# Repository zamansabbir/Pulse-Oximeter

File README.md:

# Pulse-Oximeter
This repository contains Firmware (driver) for PPG device made using PSOC1 chip to operate MAX30102 for collecting PPG signal and calculating SPO2. The device is dynamically tuned to address the technical reliability  issues involving PPG signal on people with dark skin tones.  

PPG_Firmware_6->Main.c files contains driver API for MAX30102

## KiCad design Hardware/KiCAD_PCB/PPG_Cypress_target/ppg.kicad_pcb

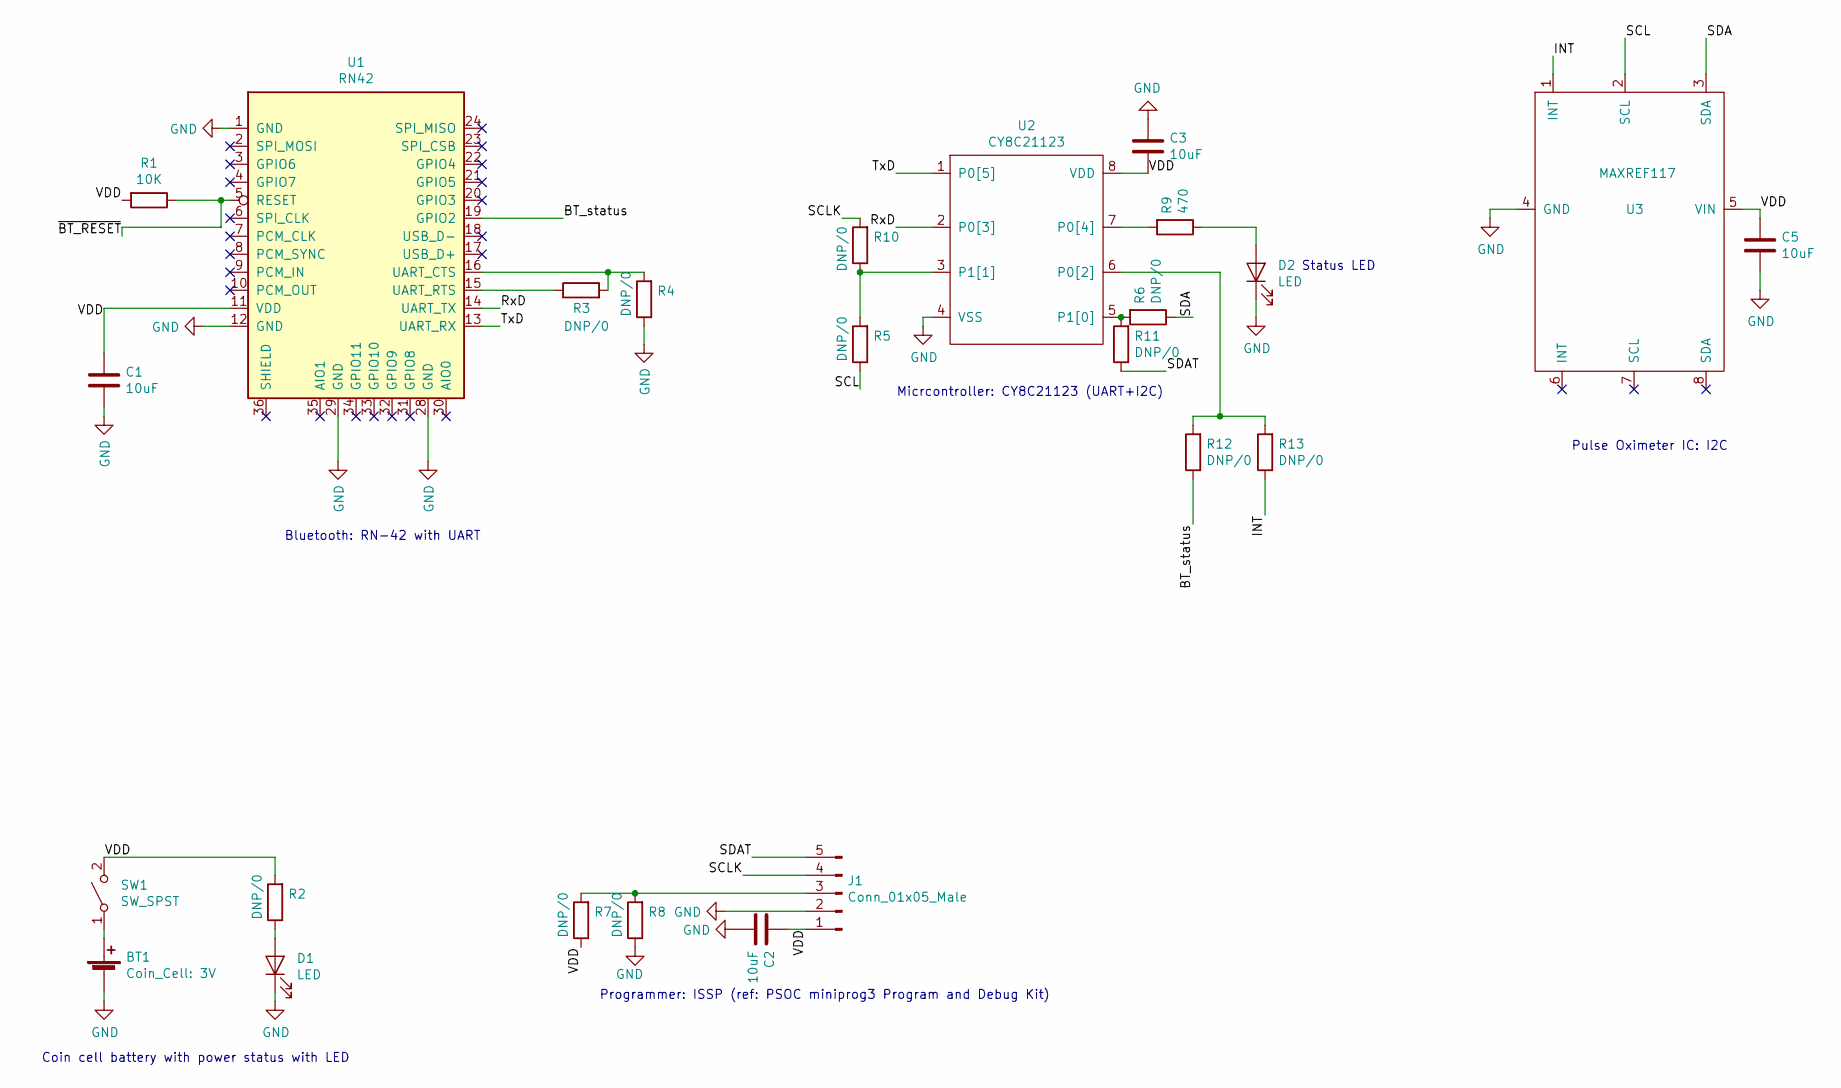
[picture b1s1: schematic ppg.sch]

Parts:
BT1: Coin_Cell: 3V; BatteryHolder_Keystone_3000_1x12mm
C1, C2, C3, C5: 10uF; C_0603_1608Metric
D1: LED; LED_0603_1608Metric_Pad1.05x0.95mm_HandSolder
D2: LED; LED_0603_1608Metric
J1: Conn_01x05_Male; Cypress_Programmer
R1: 10K; R_0603_1608Metric
R2, R3, R4, R5, R6, R7, R8, R10, R11, R12, R13: DNP/0; R_0603_1608Metric
R9: 470; R_0603_1608Metric
SW1: SW_SPST; Slide_SPDT_CK-JS102011SAQN
U1: RN42; RN42_v2
U2: CY8C21123; CY8C21123_8_SOIC
U3: MAXREF117; Pulse_Oximeter

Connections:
/BT_status: R12.1, U1.19 (GPIO2)
/INT: R13.1, U3.1 (INT)
/RxD: U1.14 (UART_TX), U2.2 (P0[3])
/SCL: R5.1, U3.2 (SCL)
/SCLK: J1.4, R10.2
/SDA: R6.1, U3.3 (SDA)
/SDAT: J1.5, R11.1
/TxD: U1.13 (UART_RX), U2.1 (P0[5])
/VDD: C1.1, C2.1, C3.2, C5.1, J1.1, R1.2, R2.2, R7.1, SW1.2 (B), U1.11 (VDD), U2.8 (VDD), U3.5 (VIN); also elsewhere on the board
/~BT_RESET: R1.1, U1.5 (RESET)
GND: BT1.2 (-), C1.2, C2.2, C3.1, C5.2, D1.1 (K), D2.1 (K), J1.2, R4.1, R8.1, U1.1 (GND), U1.12 (GND), U1.28 (GND), U1.29 (GND), U2.4 (VSS), U3.4 (GND); also elsewhere on the board
unnamed: BT1.1 (+), SW1.1 (A)
unnamed: D1.2 (A), R2.1
unnamed: D2.2 (A), R9.1
unnamed: J1.3, R7.2, R8.2
unnamed: R3.1, U1.15 (UART_RTS)
unnamed: R3.2, R4.2, U1.16 (UART_CTS)
unnamed: R9.2, U2.7 (P0[4])
unnamed: R5.2, R10.1, U2.3 (P1[1])
unnamed: R6.2, R11.2, U2.5 (P1[0])
unnamed: R12.2, R13.2, U2.6 (P0[2])

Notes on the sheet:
Programmer: ISSP (ref: PSOC miniprog3 Program and Debug Kit)
Bluetooth: RN-42 with UART
Micrcontroller: CY8C21123 (UART+I2C)
Status LED
Pulse Oximeter IC: I2C
Coin cell battery with power status with LED

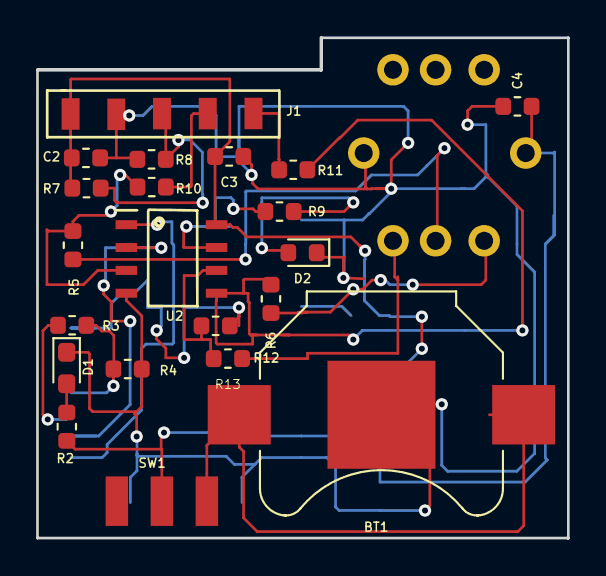
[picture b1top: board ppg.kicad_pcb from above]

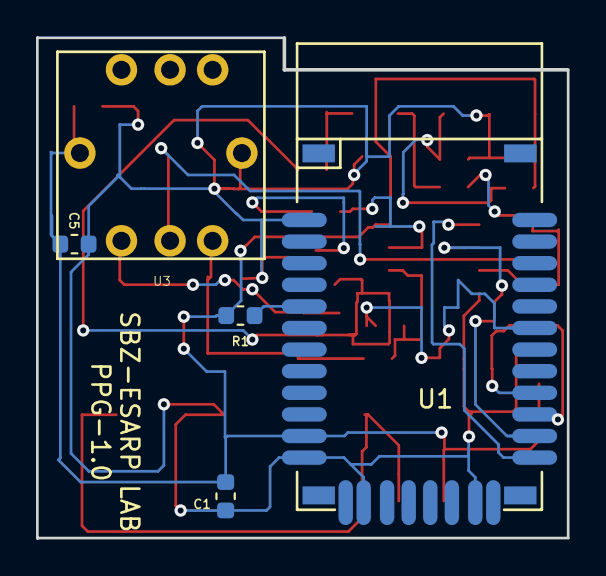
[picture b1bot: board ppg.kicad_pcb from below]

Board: 2 copper layers, 29.4 x 27.8 mm, 26 parts (5 on the bottom side), 21 nets.

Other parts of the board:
C4: 10uF; C_0603_1608Metric

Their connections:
/VDD: C4.2; also elsewhere on the board
GND: C4.1; also elsewhere on the board

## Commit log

2020-08-24 Firmware and Hardware(KiCAD project) added
2020-08-24 PPG firmware and hardware files are added
